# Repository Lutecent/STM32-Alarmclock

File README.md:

# STM32-Alarmclock

Dit is de repo voor het KBS project.

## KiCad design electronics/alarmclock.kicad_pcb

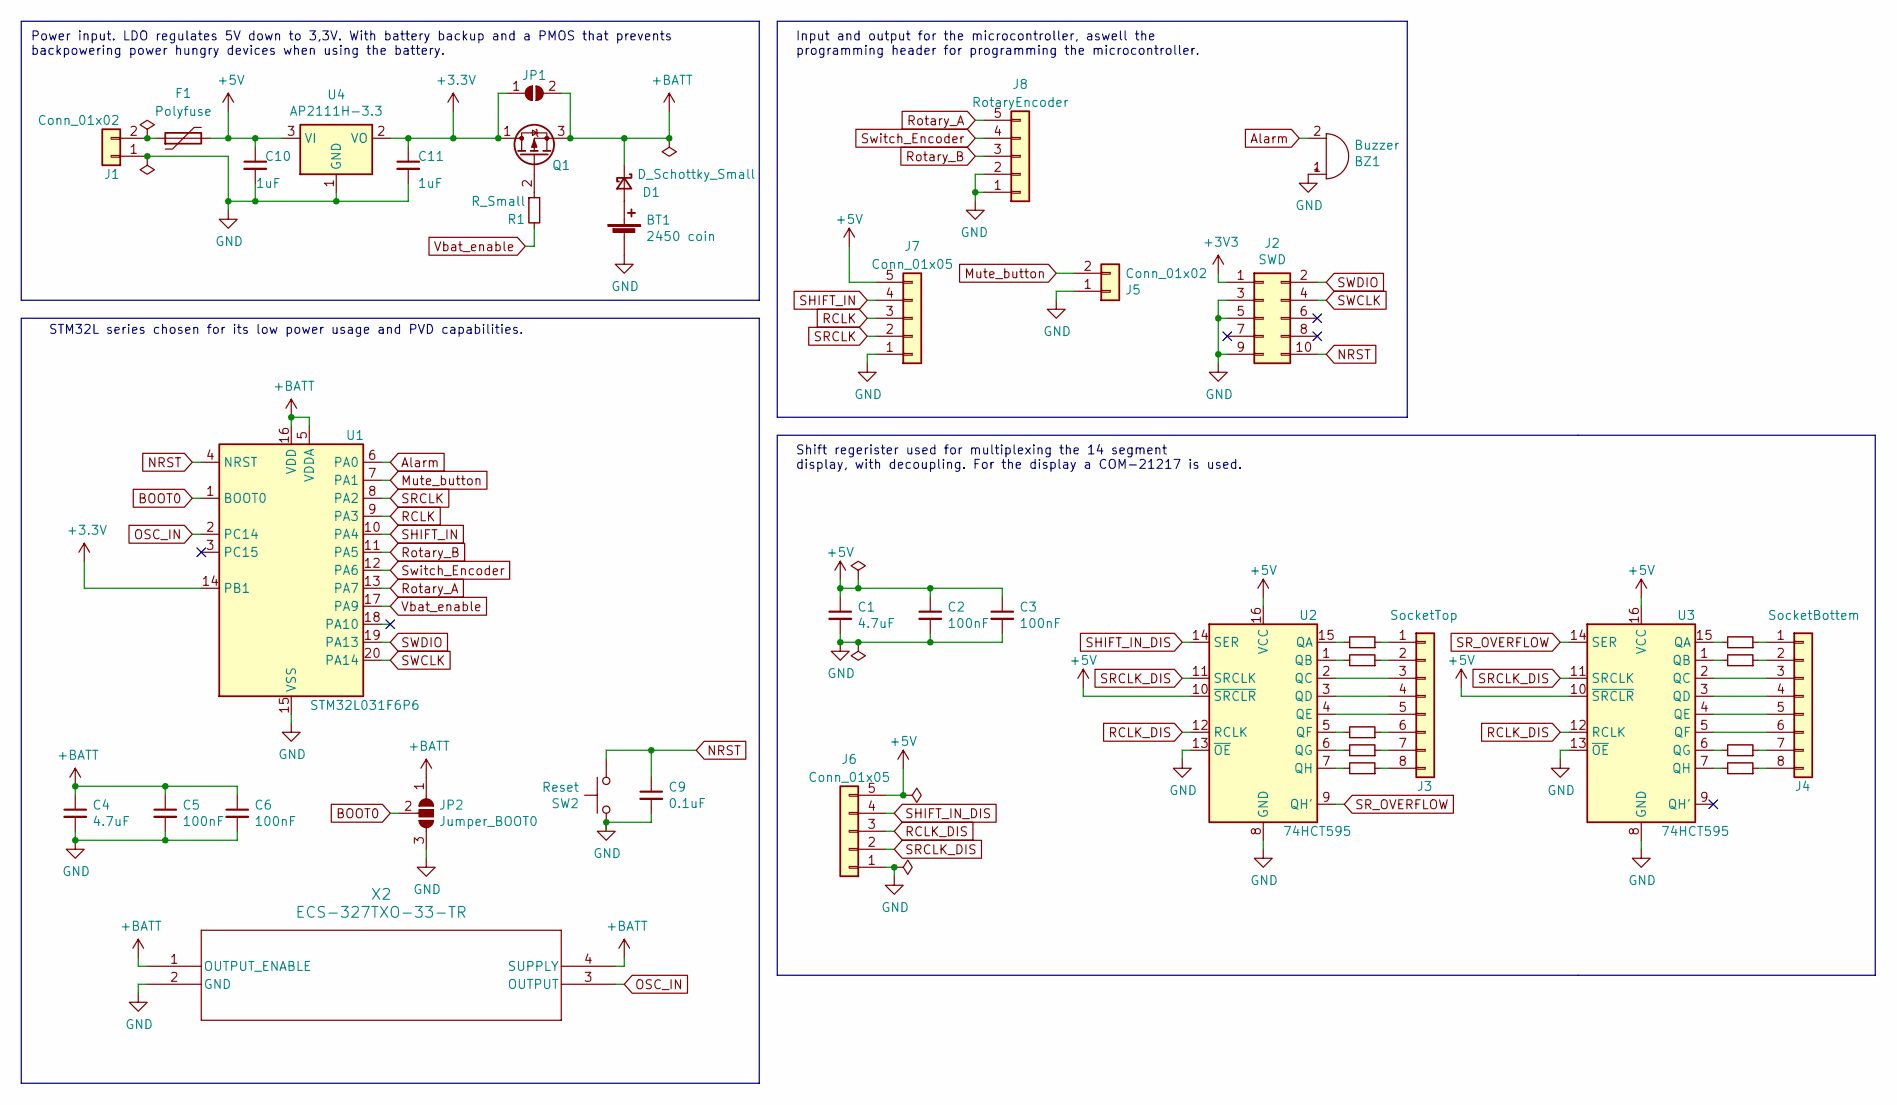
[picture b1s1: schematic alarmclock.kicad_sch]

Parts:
BT1: 2450 coin; BatteryHolder_ComfortableElectronic_CH273-2450_1x2450
BZ1: Buzzer; PinHeader_1x02_P2.54mm_Vertical
C1, C4: 4.7uF; C_1206_3216Metric
C2, C3, C5, C6: 100nF; C_1206_3216Metric
C9: 0.1uF; C_1206_3216Metric
C10, C11: 1uF; C_1206_3216Metric
D1: D_Schottky_Small; D_1206_3216Metric_Pad1.42x1.75mm_HandSolder
F1: Polyfuse; Fuse_1206_3216Metric
J1, J5: Conn_01x02; PinHeader_1x02_P2.54mm_Vertical
J2: SWD; PinHeader_2x05_P1.00mm_Vertical
J3: SocketTop; PinSocket_1x08_P2.54mm_Vertical
J4: SocketBottem; PinSocket_1x08_P2.54mm_Vertical
J6, J7: Conn_01x05; PinHeader_1x05_P2.54mm_Vertical
J8: RotaryEncoder; PinHeader_1x05_P2.54mm_Vertical
JP1: SolderJumper_2_Open; SolderJumper-2_P1.3mm_Open_TrianglePad1.0x1.5mm
JP2: Jumper_BOOT0; SolderJumper-3_P2.0mm_Open_TrianglePad1.0x1.5mm
Q1: Backpower; SOT-323_SC-70_Handsoldering
R1, R3, R4, R8, R9, R10, R11, R12, R17, R18: R_Small; R_1206_3216Metric
SW2: Reset; PinHeader_1x02_P2.54mm_Vertical
U1: STM32L031F6P6; TSSOP-20_4.4x6.5mm_P0.65mm
U2, U3: 74HCT595; TSSOP-16_4.4x5mm_P0.65mm
U4: AP2111H-3.3; SOT-223-3_TabPin2
X2: ECS-327TXO-33-TR; ECS-327_ECS

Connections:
+3.3V: C11.1, JP1.1 (A), Q1.1 (D), U1.14 (PB1), U4.2 (VO)
+3V3: J2.1
+5V: C1.1, C2.1, C3.1, C10.1, F1.2, J6.5, J7.5, U2.10 (~SRCLR), U2.16 (VCC), U3.10 (~SRCLR), U3.16 (VCC), U4.3 (VI)
+BATT: C4.1, C5.1, C6.1, D1.1 (K), JP1.2 (B), JP2.1 (A), Q1.3 (S), U1.5 (VDDA), U1.16 (VDD), X2.1 (OUTPUT_ENABLE), X2.4 (SUPPLY)
Alarm: BZ1.2 (+), U1.6 (PA0)
BOOT0: JP2.2 (C), U1.1 (BOOT0)
GND: BT1.2 (-), BZ1.1 (-), C1.2, C2.2, C3.2, C4.2, C5.2, C6.2, C9.2, C10.2, C11.2, J1.1, J2.3, J2.5, J2.9, J5.1, J6.1, J7.1, J8.1, J8.2, JP2.3 (B), SW2.1, U1.15 (VSS), U2.8 (GND), U2.13 (~OE), U3.8 (GND), U3.13 (~OE), U4.1 (GND), X2.2 (GND)
Mute_button: J5.2, U1.7 (PA1)
NRST: C9.1, J2.10, SW2.2, U1.4 (NRST)
unnamed: BT1.1 (+), D1.2 (A)
unnamed: F1.1, J1.2
unnamed: J3.1, R3.1
unnamed: J3.2, R4.1
unnamed: J3.3, U2.2 (QC)
unnamed: J3.4, U2.3 (QD)
unnamed: J3.5, U2.4 (QE)
unnamed: J3.6, R8.1
unnamed: J3.7, R10.1
unnamed: J3.8, R11.1
unnamed: J4.1, R9.1
unnamed: J4.2, R12.1
unnamed: J4.3, U3.2 (QC)
unnamed: J4.4, U3.3 (QD)
unnamed: J4.5, U3.4 (QE)
unnamed: J4.6, U3.5 (QF)
unnamed: J4.7, R17.1
unnamed: J4.8, R18.1
unnamed: Q1.2 (G), R1.1
unnamed: R3.2, U2.15 (QA)
unnamed: R4.2, U2.1 (QB)
unnamed: R8.2, U2.5 (QF)
unnamed: R10.2, U2.6 (QG)
unnamed: R11.2, U2.7 (QH)
unnamed: R9.2, U3.15 (QA)
unnamed: R12.2, U3.1 (QB)
unnamed: R17.2, U3.6 (QG)
unnamed: R18.2, U3.7 (QH)
OSC_IN: U1.2 (PC14), X2.3 (OUTPUT)
RCLK: J7.3, U1.9 (PA3)
RCLK_DIS: J6.3, U2.12 (RCLK), U3.12 (RCLK)
Rotary_A: J8.5, U1.13 (PA7)
Rotary_B: J8.3, U1.11 (PA5)
SHIFT_IN: J7.4, U1.10 (PA4)
SHIFT_IN_DIS: J6.4, U2.14 (SER)
SRCLK: J7.2, U1.8 (PA2)
SRCLK_DIS: J6.2, U2.11 (SRCLK), U3.11 (SRCLK)
SR_OVERFLOW: U2.9 (QH'), U3.14 (SER)
SWCLK: J2.4, U1.20 (PA14)
SWDIO: J2.2, U1.19 (PA13)
Switch_Encoder: J8.4, U1.12 (PA6)
Vbat_enable: R1.2, U1.17 (PA9)

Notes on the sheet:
Power input. LDO regulates 5V down to 3,3V. With battery backup and a PMOS that prevents backpowering power hungry devices when using the battery.
Input and output for the microcontroller, aswell the programming header for programming the microcontroller.
STM32L series chosen for its low power usage and PVD capabilities.
Shift regerister used for multiplexing the 14 segment display, with decoupling. For the display a COM-21217 is used.

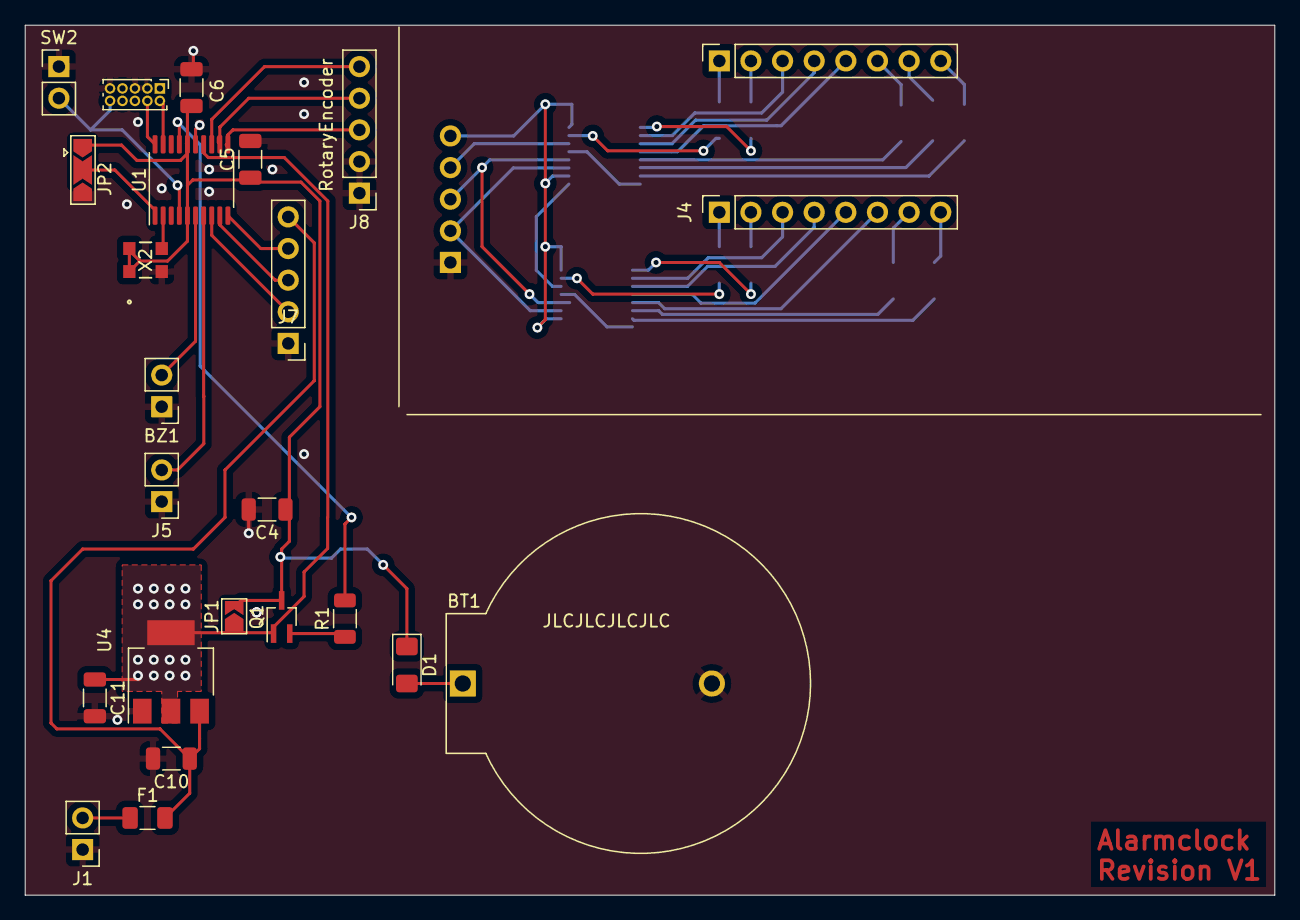
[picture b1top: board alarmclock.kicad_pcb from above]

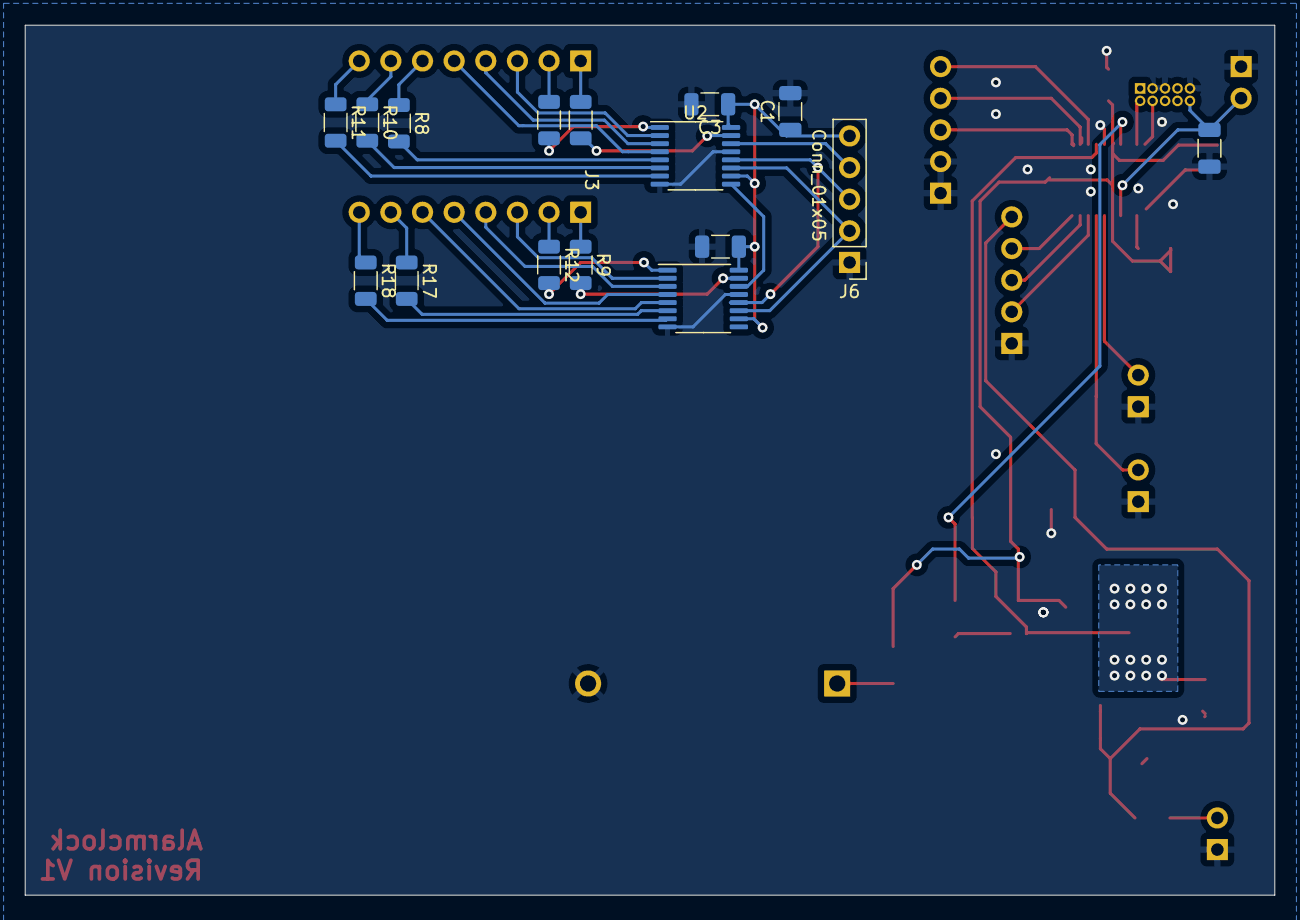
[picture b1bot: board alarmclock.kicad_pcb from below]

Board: 2 copper layers, 100.3 x 69.9 mm, 40 parts (16 on the bottom side), 50 nets.

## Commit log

2023-01-17 feat: first schematics
2023-01-17 feat: CubeMX pinassignment and small schemetic changes
2023-01-18 added headers for connecting the display, made first pcb layout
2023-01-19 refined pinout, changed solder pad sizes
2023-01-19 forgot to save
2023-02-23 reverted previous commit, as it removed the schematic
2023-03-07 pcb over de zeik
2023-03-07 ook een netlist werkt
2023-03-09 feature: new microprossesor for beter low power performance and smaller footprint
2023-03-11 added beginning of battery backup
2023-03-11 minor changes
2023-03-12 added docs
2023-03-17 yet another microcontroller switch. added shiftregisters, added battery backup
2023-03-18 add 5v rail and voltage regulator
2023-03-19 updated to kicad 7
2023-04-04 added currentlimiting resistors
2023-04-19 made most of the pcb
2023-04-21 finilised for review
2023-05-29 Changed the pcblayout after learning more about ground
2023-10-18 tape out
